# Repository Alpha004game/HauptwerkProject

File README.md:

# HauptwerkProject

**STATUS: on going**

Progetto open source per la gestione di una pedaliera MIDI, staffe di espressione e bottoniera compatibili con [Hauptwerk](https://www.hauptwerk.com/), basato su Arduino Pro Micro (ATmega32U4). Il sistema invia messaggi MIDI tramite USB grazie alla libreria `MIDIUSB.h`.

## Contenuto del Progetto

- pedaliera a 30/32 note tramite shift register 74HC165
- **3 Staffe di espressione** analogiche con LED indicatori a segmenti (shift register 74HC595)
- Bottoniera per pedaletti e pulsantini sulle tastiere
- **Output MIDI-USB** compatibile con Hauptwerk, GrandOrgue, o qualsiasi DAW

## Requisiti Hardware

- Arduino Pro Micro (ATmega32U4) – obbligatorio per la libreria MIDIUSB X2
- Shift register 74HC165 (input bottoniera) X8
- Shift register 74HC595 (output LED staffe) X3
- potenziometri lineari o sensori analogici per staffe X3
- contattiera per pedaliera di tipo reed switch o sensori hall X30/x32
- LED per visualizzazione livelli staffa (opzionale) X24

### Librerie Arduino
Assicurati di avere installato:

- [`MIDIUSB`](https://github.com/arduino-libraries/MIDIUSB) (via Library Manager)

## 👤 Autore

**Francesco Patti**  
[GitHub](https://github.com/Alpha004game)

🔗 *Compatibile con Hauptwerk™, GrandOrgue, Reaper, Kontakt, e qualsiasi DAW/MIDI host.*

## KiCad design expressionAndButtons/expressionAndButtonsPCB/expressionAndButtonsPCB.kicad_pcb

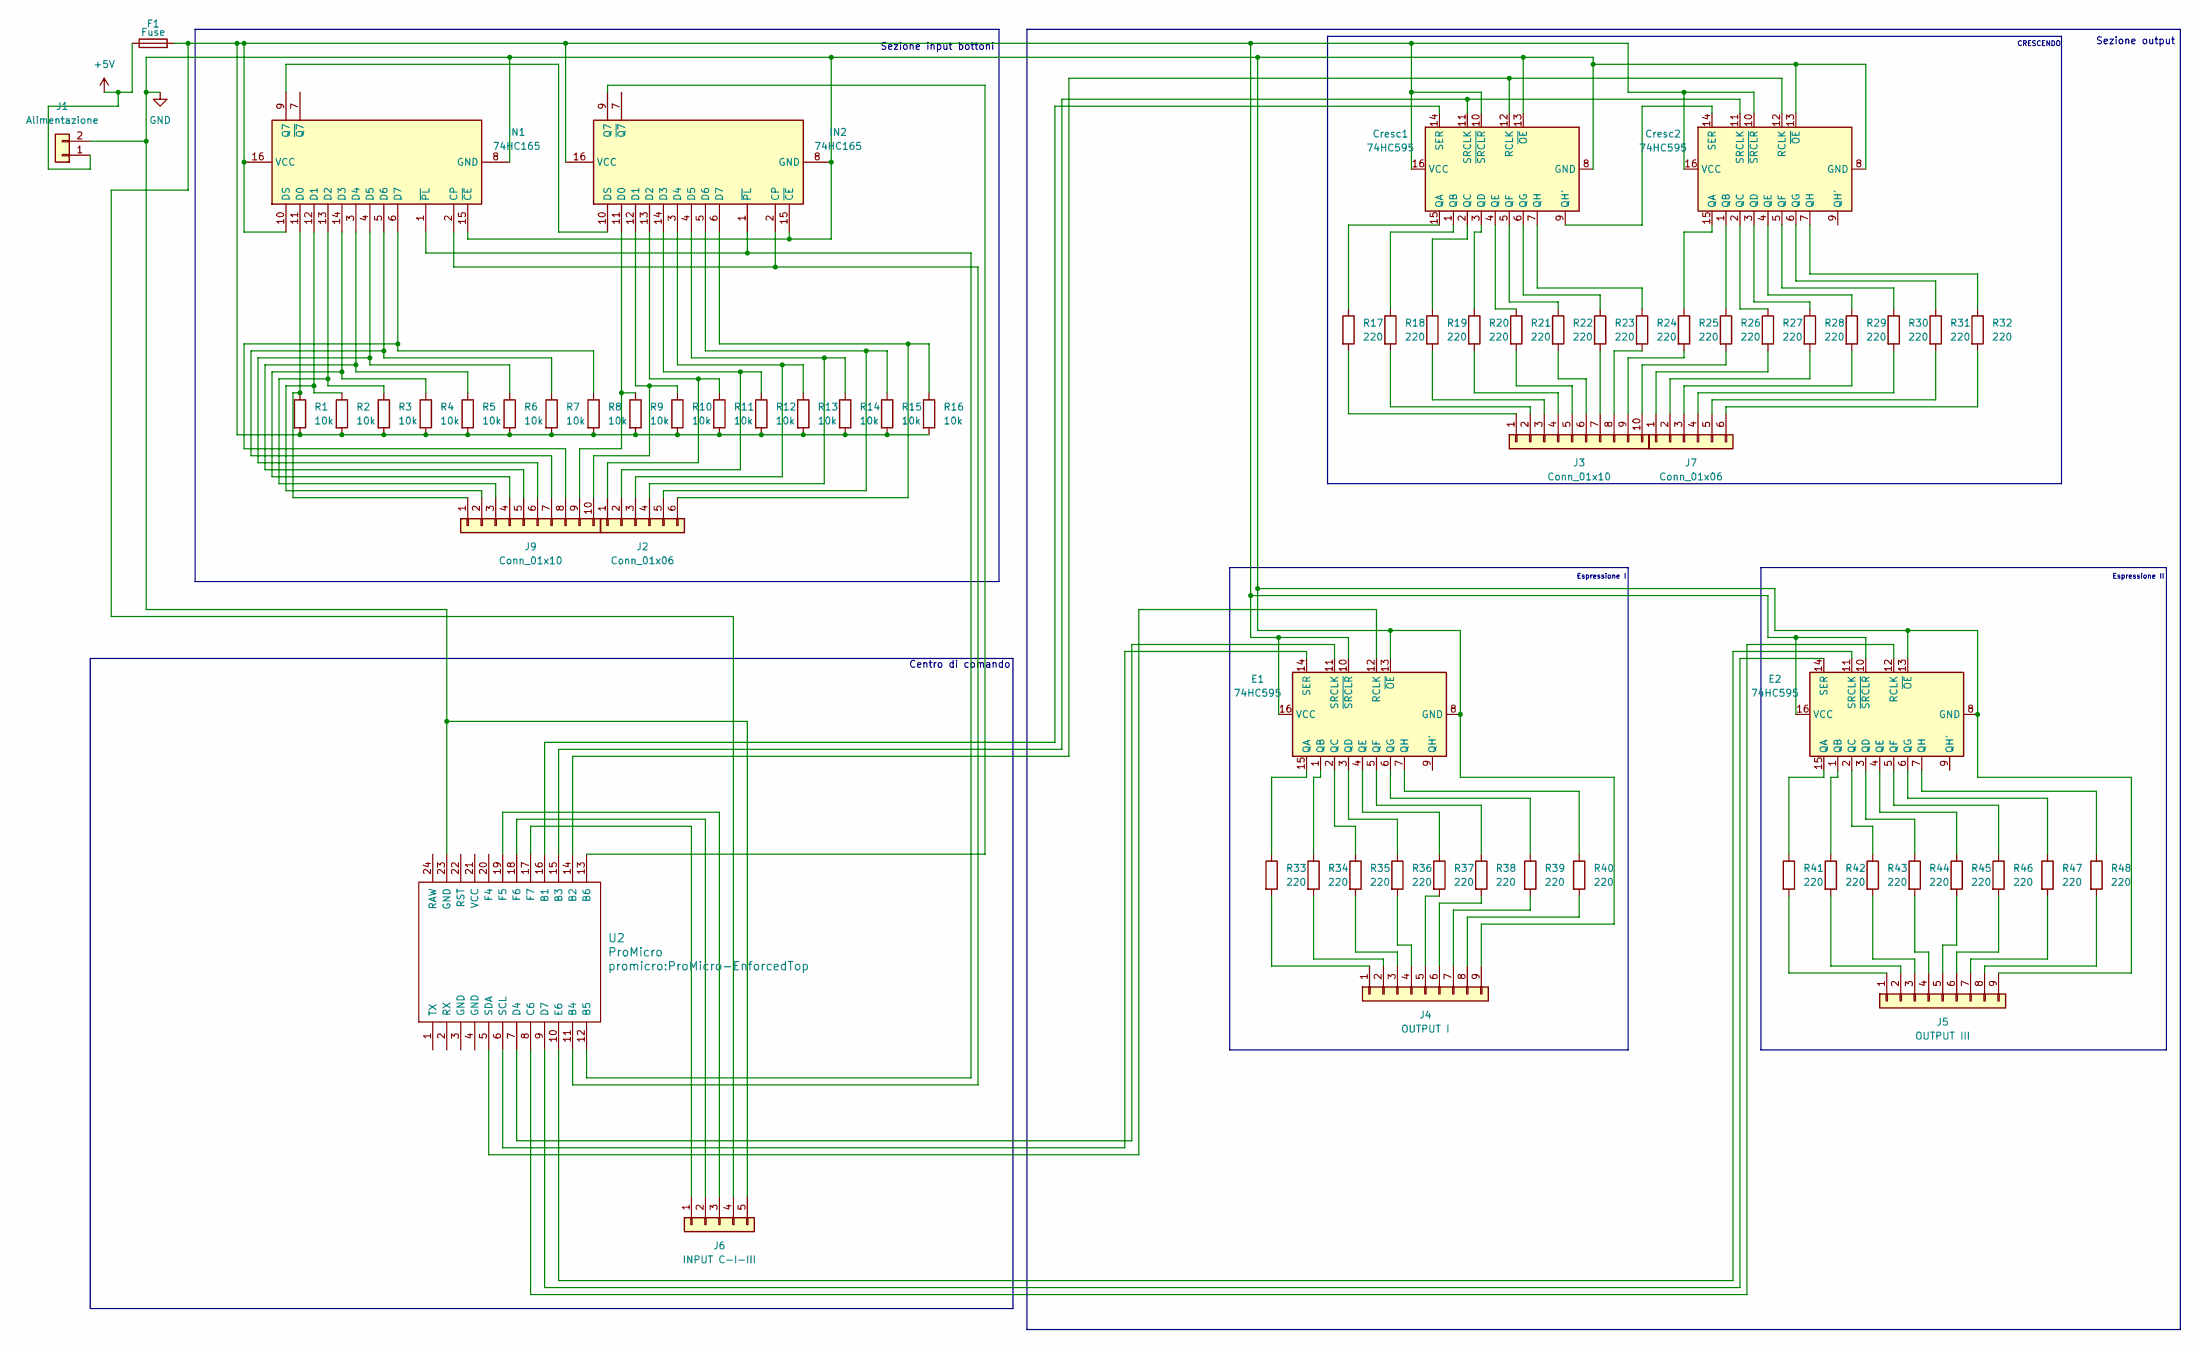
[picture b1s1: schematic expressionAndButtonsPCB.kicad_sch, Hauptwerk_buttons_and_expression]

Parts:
Cresc1, Cresc2: 74HC595; DIP-16_W7.62mm
E1, E2: 74HC595; DIP-16_W7.62mm
F1: Fuse; Fuseholder_Cylinder-5x20mm_Schurter_0031_8201_Horizontal_Op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
IN1, IN2: 74HC165; DIP-16_W7.62mm
J1: Alimentazione; TerminalBlock_Phoenix_MPT-0,5-2-2.54_1x02_P2.54mm_Horizontal
J2, J7: Conn_01x06; TerminalBlock_Phoenix_MPT-0,5-6-2.54_1x06_P2.54mm_Horizontal
J3, J9: Conn_01x10; TerminalBlock_Phoenix_MPT-0,5-10-2.54_1x10_P2.54mm_Horizont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
J4: OUTPUT I; TerminalBlock_Phoenix_MPT-0,5-9-2.54_1x09_P2.54mm_Horizontal
J5: OUTPUT III; TerminalBlock_Phoenix_MPT-0,5-9-2.54_1x09_P2.54mm_Horizontal
J6: INPUT C-I-III; TerminalBlock_Phoenix_MPT-0,5-5-2.54_1x05_P2.54mm_Horizontal
R1, R2, R3, R4, R5, R6, R7, R8, R9, R10, R11, R12, R13, R14, R15, R16: 10k; R_Axial_DIN0207_L6.3mm_D2.5mm_P7.62mm_Horizontal
R17, R18, R19, R20, R21, R22, R23, R24, R25, R26, R27, R28, R29, R30, R31, R32, R33, R34, R35, R36, R37, R38, R39, R40, R41, R42, R43, R44, R45, R46, R47, R48: 220; R_Axial_DIN0207_L6.3mm_D2.5mm_P7.62mm_Horizontal
U2: ProMicro; ProMicro-EnforcedTop

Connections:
+5V: F1.1, J1.1
GND: Cresc1.8 (GND), Cresc1.13 (~OE), Cresc2.8 (GND), Cresc2.13 (~OE), E1.8 (GND), E1.13 (~OE), E2.8 (GND), E2.13 (~OE), IN1.8 (GND), IN1.15 (~CE), IN2.8 (GND), IN2.15 (~CE), J1.2, J4.9, J5.9, J6.5, U2.23 (GND)
unnamed: Cresc1.15 (QA), R17.1
unnamed: Cresc1.1 (QB), R18.1
unnamed: Cresc1.2 (QC), R19.1
unnamed: Cresc1.3 (QD), R20.1
unnamed: Cresc1.4 (QE), R21.1
unnamed: Cresc1.5 (QF), R22.1
unnamed: Cresc1.6 (QG), R23.1
unnamed: Cresc1.9 (QH'), Cresc2.14 (SER)
unnamed: Cresc1.7 (QH), R24.1
unnamed: Cresc1.12 (RCLK), Cresc2.12 (RCLK), U2.14 (B2)
unnamed: Cresc1.14 (SER), U2.16 (B1)
unnamed: Cresc1.11 (SRCLK), Cresc2.11 (SRCLK), U2.15 (B3)
unnamed: Cresc1.10 (~SRCLR), Cresc1.16 (VCC), Cresc2.10 (~SRCLR), Cresc2.16 (VCC), E1.10 (~SRCLR), E1.16 (VCC), E2.10 (~SRCLR), E2.16 (VCC), F1.2, IN1.10 (DS), IN1.16 (VCC), IN2.16 (VCC), J6.4, R1.2, R2.2, R3.2, R4.2, R5.2, R6.2, R7.2, R8.2, R9.2, R10.2, R11.2, R12.2, R13.2, R14.2, R15.2, R16.2
unnamed: Cresc2.15 (QA), R25.1
unnamed: Cresc2.1 (QB), R26.1
unnamed: Cresc2.2 (QC), R27.1
unnamed: Cresc2.3 (QD), R28.1
unnamed: Cresc2.4 (QE), R29.1
unnamed: Cresc2.5 (QF), R30.1
unnamed: Cresc2.6 (QG), R31.1
unnamed: Cresc2.7 (QH), R32.1
unnamed: E1.15 (QA), R33.1
unnamed: E1.1 (QB), R34.1
unnamed: E1.2 (QC), R35.1
unnamed: E1.3 (QD), R36.1
unnamed: E1.4 (QE), R37.1
unnamed: E1.5 (QF), R38.1
unnamed: E1.6 (QG), R39.1
unnamed: E1.7 (QH), R40.1
unnamed: E1.12 (RCLK), U2.5 (SDA)
unnamed: E1.14 (SER), U2.6 (SCL)
unnamed: E1.11 (SRCLK), U2.7 (D4)
unnamed: E2.15 (QA), R41.1
unnamed: E2.1 (QB), R42.1
unnamed: E2.2 (QC), R43.1
unnamed: E2.3 (QD), R44.1
unnamed: E2.4 (QE), R45.1
unnamed: E2.5 (QF), R46.1
unnamed: E2.6 (QG), R47.1
unnamed: E2.7 (QH), R48.1
unnamed: E2.12 (RCLK), U2.8 (C6)
unnamed: E2.14 (SER), U2.9 (D7)
unnamed: E2.11 (SRCLK), U2.10 (E6)
unnamed: IN1.2 (CP), IN2.2 (CP), U2.11 (B4)
unnamed: IN1.11 (D0), J9.1, R1.1
unnamed: IN1.12 (D1), J9.2, R2.1
unnamed: IN1.13 (D2), J9.3, R3.1
unnamed: IN1.14 (D3), J9.4, R4.1
unnamed: IN1.3 (D4), J9.5, R5.1
unnamed: IN1.4 (D5), J9.6, R6.1
unnamed: IN1.5 (D6), J9.7, R7.1
unnamed: IN1.6 (D7), J9.8, R8.1
unnamed: IN1.9 (Q7), IN2.10 (DS)
unnamed: IN1.1 (~PL), IN2.1 (~PL), U2.12 (B5)
unnamed: IN2.11 (D0), J9.9, R9.1
unnamed: IN2.12 (D1), J9.10, R10.1
unnamed: IN2.13 (D2), J2.1, R11.1
unnamed: IN2.14 (D3), J2.2, R12.1
unnamed: IN2.3 (D4), J2.3, R13.1
unnamed: IN2.4 (D5), J2.4, R14.1
unnamed: IN2.5 (D6), J2.5, R15.1
unnamed: IN2.6 (D7), J2.6, R16.1
unnamed: IN2.9 (Q7), U2.13 (B6)
unnamed: J3.1, R17.2
unnamed: J3.2, R18.2
unnamed: J3.3, R19.2
unnamed: J3.4, R20.2
unnamed: J3.5, R21.2
unnamed: J3.6, R22.2
unnamed: J3.7, R23.2
unnamed: J3.8, R24.2
unnamed: J3.9, R25.2
unnamed: J3.10, R26.2
unnamed: J4.1, R33.2
unnamed: J4.2, R34.2
unnamed: J4.3, R35.2
unnamed: J4.4, R36.2
unnamed: J4.5, R37.2
unnamed: J4.6, R38.2
unnamed: J4.7, R39.2
unnamed: J4.8, R40.2
unnamed: J5.1, R41.2
unnamed: J5.2, R42.2
unnamed: J5.3, R43.2
unnamed: J5.4, R44.2
unnamed: J5.5, R45.2
unnamed: J5.6, R46.2
unnamed: J5.7, R47.2
unnamed: J5.8, R48.2
unnamed: J6.1, U2.17 (F7)
unnamed: J6.2, U2.18 (F6)
unnamed: J6.3, U2.19 (F5)
unnamed: J7.1, R27.2
unnamed: J7.2, R28.2
unnamed: J7.3, R29.2
unnamed: J7.4, R30.2
unnamed: J7.5, R31.2
unnamed: J7.6, R32.2

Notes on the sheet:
Espressione I
CRESCENDO
Sezione output
Centro di comando
Sezione input bottoni
Espressione II

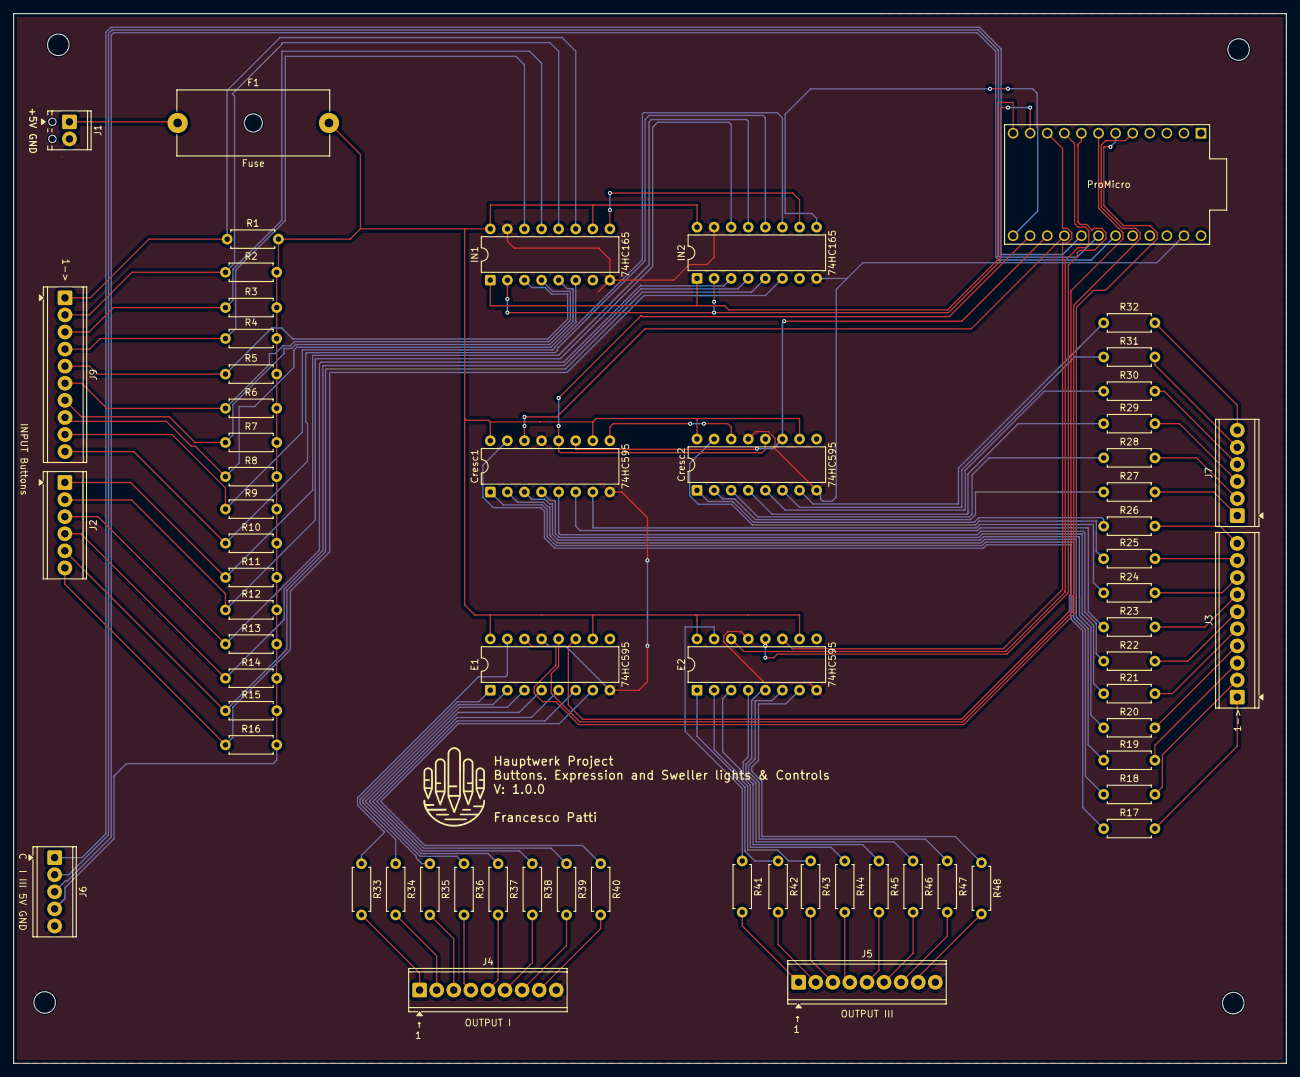
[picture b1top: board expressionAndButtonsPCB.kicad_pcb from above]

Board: 2 copper layers, 189.2 x 156.1 mm, 64 parts (0 on the bottom side), 100 nets.

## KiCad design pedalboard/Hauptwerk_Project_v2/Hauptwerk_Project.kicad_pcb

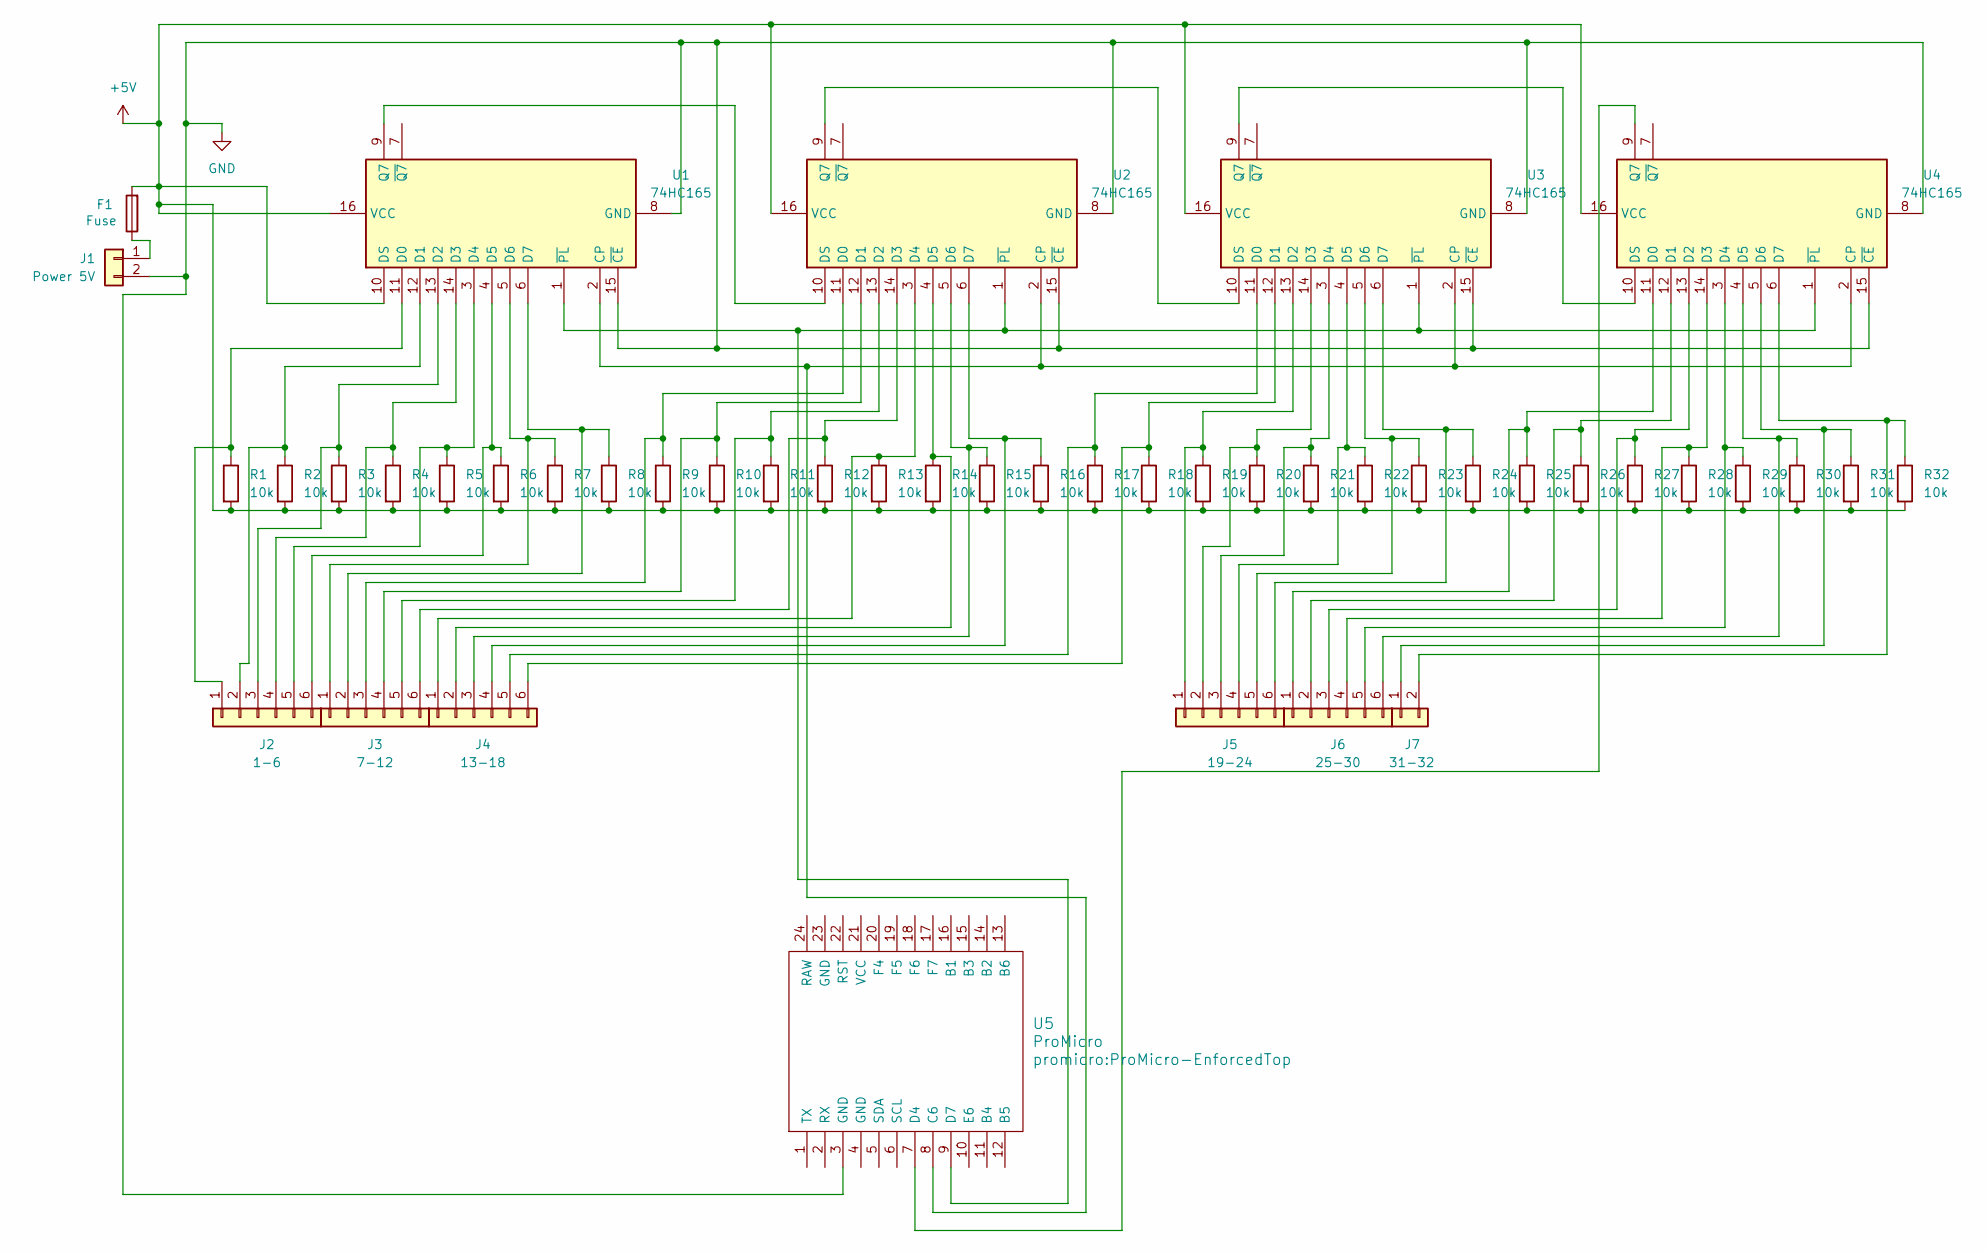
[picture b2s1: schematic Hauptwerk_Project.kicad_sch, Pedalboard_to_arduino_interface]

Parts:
F1: Fuse; Fuseholder_Cylinder-5x20mm_Schurter_0031_8201_Horizontal_Op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
J1: Power 5V; TerminalBlock_Phoenix_MKDS-1,5-2-5.08_1x02_P5.08mm_Horizont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
J2: 1-6; TerminalBlock_Phoenix_MKDS-1,5-6-5.08_1x06_P5.08mm_Horizont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
J3: 7-12; TerminalBlock_Phoenix_MKDS-1,5-6-5.08_1x06_P5.08mm_Horizont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
J4: 13-18; TerminalBlock_Phoenix_MKDS-1,5-6-5.08_1x06_P5.08mm_Horizont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
J5: 19-24; TerminalBlock_Phoenix_MKDS-1,5-6-5.08_1x06_P5.08mm_Horizont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
J6: 25-30; TerminalBlock_Phoenix_MKDS-1,5-6-5.08_1x06_P5.08mm_Horizont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
J7: 31-32; TerminalBlock_Phoenix_MKDS-1,5-2-5.08_1x02_P5.08mm_Horizont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
R1, R2, R3, R4, R5, R6, R7, R8, R9, R10, R11, R12, R13, R14, R15, R16, R17, R18, R19, R20, R21, R22, R23, R24, R25, R26, R27, R28, R29, R30, R31, R32: 10k; R_Axial_DIN0207_L6.3mm_D2.5mm_P7.62mm_Horizontal
U1, U2, U3, U4: 74HC165; DIP-16_W7.62mm
U5: ProMicro; ProMicro-EnforcedTop

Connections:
+5V: F1.2, R1.2, R2.2, R3.2, R4.2, R5.2, R6.2, R7.2, R8.2, R9.2, R10.2, R11.2, R12.2, R13.2, R14.2, R15.2, R16.2, R17.2, R18.2, R19.2, R20.2, R21.2, R22.2, R23.2, R24.2, R25.2, R26.2, R27.2, R28.2, R29.2, R30.2, R31.2, R32.2, U1.10 (DS), U1.16 (VCC), U2.16 (VCC), U3.16 (VCC), U4.16 (VCC)
GND: J1.2, U1.8 (GND), U1.15 (~CE), U2.8 (GND), U2.15 (~CE), U3.8 (GND), U3.15 (~CE), U4.8 (GND), U4.15 (~CE), U5.3 (GND)
unnamed: F1.1, J1.1
unnamed: J2.1, R1.1, U1.11 (D0)
unnamed: J2.2, R2.1, U1.12 (D1)
unnamed: J2.3, R3.1, U1.13 (D2)
unnamed: J2.4, R4.1, U1.14 (D3)
unnamed: J2.5, R5.1, U1.3 (D4)
unnamed: J2.6, R6.1, U1.4 (D5)
unnamed: J3.1, R7.1, U1.5 (D6)
unnamed: J3.2, R8.1, U1.6 (D7)
unnamed: J3.3, R9.1, U2.11 (D0)
unnamed: J3.4, R10.1, U2.12 (D1)
unnamed: J3.5, R11.1, U2.13 (D2)
unnamed: J3.6, R12.1, U2.14 (D3)
unnamed: J4.1, R13.1, U2.3 (D4)
unnamed: J4.2, R14.1, U2.4 (D5)
unnamed: J4.3, R15.1, U2.5 (D6)
unnamed: J4.4, R16.1, U2.6 (D7)
unnamed: J4.5, R17.1, U3.11 (D0)
unnamed: J4.6, R18.1, U3.12 (D1)
unnamed: J5.1, R19.1, U3.13 (D2)
unnamed: J5.2, R20.1, U3.14 (D3)
unnamed: J5.3, R21.1, U3.3 (D4)
unnamed: J5.4, R22.1, U3.4 (D5)
unnamed: J5.5, R23.1, U3.5 (D6)
unnamed: J5.6, R24.1, U3.6 (D7)
unnamed: J6.1, R25.1, U4.11 (D0)
unnamed: J6.2, R26.1, U4.12 (D1)
unnamed: J6.3, R27.1, U4.13 (D2)
unnamed: J6.4, R28.1, U4.14 (D3)
unnamed: J6.5, R29.1, U4.3 (D4)
unnamed: J6.6, R30.1, U4.4 (D5)
unnamed: J7.1, R31.1, U4.5 (D6)
unnamed: J7.2, R32.1, U4.6 (D7)
unnamed: U1.2 (CP), U2.2 (CP), U3.2 (CP), U4.2 (CP), U5.8 (C6)
unnamed: U1.9 (Q7), U2.10 (DS)
unnamed: U1.1 (~PL), U2.1 (~PL), U3.1 (~PL), U4.1 (~PL), U5.9 (D7)
unnamed: U2.9 (Q7), U3.10 (DS)
unnamed: U3.9 (Q7), U4.10 (DS)
unnamed: U4.9 (Q7), U5.7 (D4)

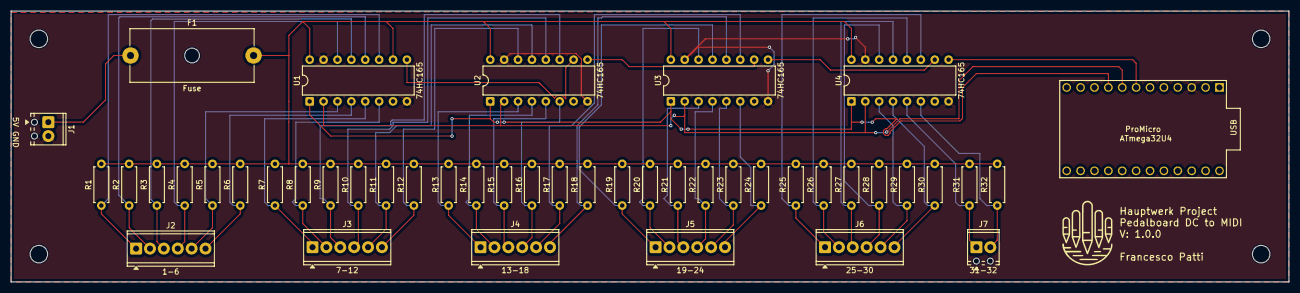
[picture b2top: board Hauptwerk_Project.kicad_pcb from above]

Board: 2 copper layers, 233.7 x 49.5 mm, 45 parts (0 on the bottom side), 41 nets.

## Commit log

2025-07-31 Creazione PCB
    Prima versione creata e qualche sistemazione nello schema elettrico
2025-07-31 Add logo
2025-08-02 Aggiornamento e creazione versione con arduino integrato
2025-08-02 Creazione progetto per staffe e bottoniera
2025-08-11 Fix vari
2025-08-11 check
2025-08-28 Update dim footprint
2025-09-01 Progresso bottoniera
2025-09-02 First version buttons
2025-09-10 problem fix
2025-09-22 Add project status to README
    Added project status to README.

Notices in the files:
pedalboard/Hauptwerk_Project/Hauptwerk_Project.kicad_sch:
Copyright (c) 2025
